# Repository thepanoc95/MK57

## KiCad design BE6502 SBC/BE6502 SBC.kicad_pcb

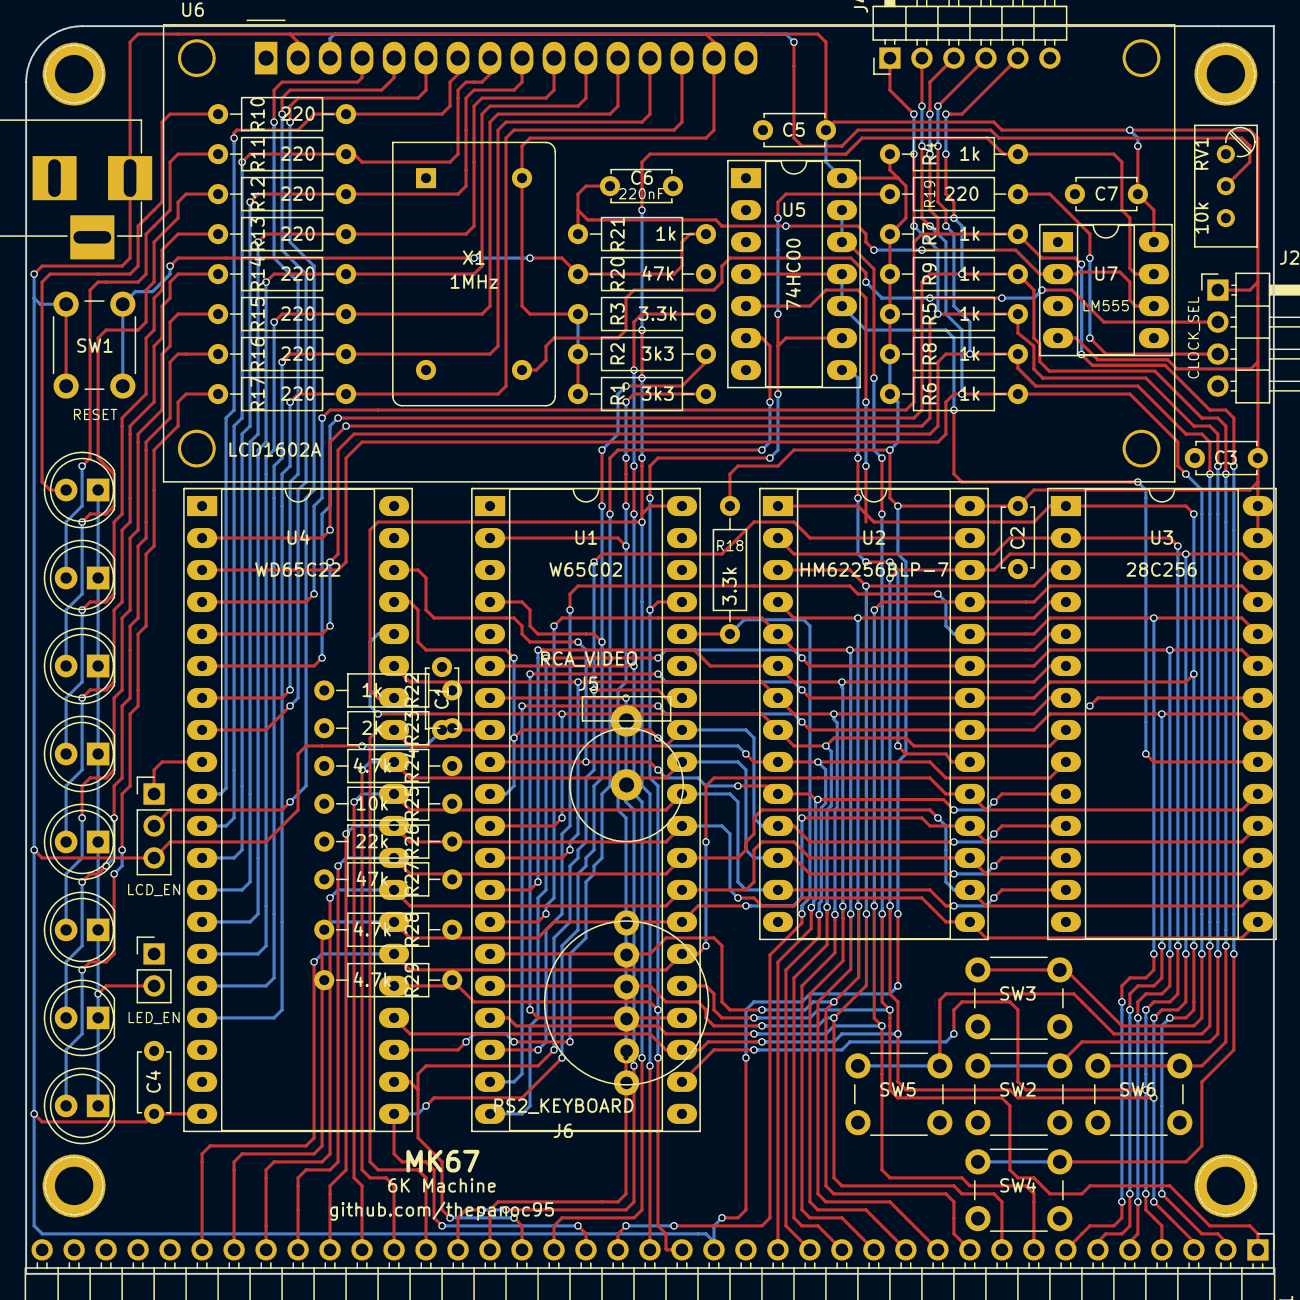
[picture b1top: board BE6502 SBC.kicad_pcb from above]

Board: 2 copper layers, 99.1 x 99.1 mm, 71 parts (0 on the bottom side), 68 nets.

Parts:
C1, C2, C3, C4, C5, C7: 100nF; C_Disc_D4.7mm_W2.5mm_P5.00mm
C6: 220nF; C_Disc_D4.7mm_W2.5mm_P5.00mm
D1, D2, D3, D4, D5, D6, D7, D8: LED; LED_D5.0mm
J1: Expansion; Pin_Header_Angled_1x39_Pitch2.54mm
J2: CLOCK_SEL; Pin_Header_Angled_1x04_Pitch2.54mm
J3: BARREL_JACK
J4: Control; Pin_Header_Angled_1x06_Pitch2.54mm
J5: RCA_VIDEO; RCA_Phono_THT
J6: PS2_KEYBOARD; PS2-6P_MiniDIN_THT
JP1: LED_EN; Pin_Header_Straight_1x02_Pitch2.54mm
JP2: LCD_EN; Pin_Header_Straight_1x03_Pitch2.54mm
M1, M2, M3, M4: Mounting; 1pin
R1, R2: 3k3; R_Axial_DIN0207_L6.3mm_D2.5mm_P10.16mm_Horizontal
R3, R18: 3.3k; R_Axial_DIN0207_L6.3mm_D2.5mm_P10.16mm_Horizontal
R4, R5, R6, R7, R8, R9, R21, R22: 1k; R_Axial_DIN0207_L6.3mm_D2.5mm_P10.16mm_Horizontal
R10, R11, R12, R13, R14, R15, R16, R17, R19: 220; R_Axial_DIN0207_L6.3mm_D2.5mm_P10.16mm_Horizontal
R20, R27: 47k; R_Axial_DIN0207_L6.3mm_D2.5mm_P10.16mm_Horizontal
R23: 2k; R_Axial_DIN0207_L6.3mm_D2.5mm_P10.16mm_Horizontal
R24, R28, R29: 4.7k; R_Axial_DIN0207_L6.3mm_D2.5mm_P10.16mm_Horizontal
R25: 10k; R_Axial_DIN0207_L6.3mm_D2.5mm_P10.16mm_Horizontal
R26: 22k; R_Axial_DIN0207_L6.3mm_D2.5mm_P10.16mm_Horizontal
RV1: 10k; Potentiometer_Trimmer_Bourns_3296W
SW1: RESET; SW_PUSH_6mm
SW2: MIDDLE; SW_PUSH_6mm
SW3: UP; SW_PUSH_6mm
SW4: DOWN; SW_PUSH_6mm
SW5: LEFT; SW_PUSH_6mm
SW6: RIGHT; SW_PUSH_6mm
U1: W65C02; DIP-40_W15.24mm_Socket_LongPads
U2: HM62256BLP-7; DIP-28_W15.24mm_Socket_LongPads
U3: 28C256; DIP-28_W15.24mm_Socket_LongPads
U4: WD65C22; DIP-40_W15.24mm_Socket_LongPads
U5: 74HC00; DIP-14_W7.62mm_Socket_LongPads
U6: RC1602A; WC1602A
U7: LM555; DIP-8_W7.62mm_Socket_LongPads
X1: 1MHz; Oscillator_DIP-14

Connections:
/A0: J1.16, U1.9, U2.10, U3.10, U4.38
/A1: J1.15, U1.10, U2.9, U3.9, U4.37
/A2: J1.14, U1.11, U2.8, U3.8, U4.36
/A3: J1.13, U1.12, U2.7, U3.7, U4.35
/A4: J1.12, U1.13, U2.6, U3.6
/A5: J1.11, U1.14, U2.5, U3.5
/A6: J1.10, U1.15, U2.4, U3.4
/A7: J1.9, U1.16, U2.3, U3.3
/A8: J1.8, U1.17, U2.25, U3.25
/A9: J1.7, U1.18, U2.24, U3.24
/A10: J1.6, U1.19, U2.21, U3.21
/A11: J1.5, U1.20, U2.23, U3.23
/A12: J1.4, U1.22, U2.2, U3.2
/A13: J1.3, U1.23, U2.26, U3.26, U4.24
/A14: J1.2, U1.24, U2.1, U2.22, U3.1, U5.5
/A15: J1.1, U1.25, U5.12, U5.13
/BE: J1.21, R18.1, U1.36
/D0: J1.27, U1.33, U2.11, U3.11, U4.33
/D1: J1.28, U1.32, U2.12, U3.12, U4.32
/D2: J1.29, U1.31, U2.13, U3.13, U4.31
/D3: J1.30, U1.30, U2.15, U3.15, U4.30
/D4: J1.31, U1.29, U2.16, U3.16, U4.29
/D5: J1.32, U1.28, U2.17, U3.17, U4.28
/D6: J1.33, U1.27, U2.18, U3.18, U4.27
/D7: J1.34, U1.26, U2.19, U3.19, U4.26
/PA0: J4.1, R5.2, R22.1, SW2.1, U4.2
/PA1: J4.2, R6.2, R23.1, SW3.1, U4.3
/PA2: J4.3, R7.2, R24.1, SW4.1, U4.4
/PA3: J4.4, R8.2, R25.1, SW5.1, U4.5
/PA4: J4.5, R9.2, R26.1, SW6.1, U4.6
/PA5: R27.1, U4.7, U6.4
/PA6: J6.1, R28.1, U4.8, U6.5
/PA7: J6.5, JP2.1, R29.1, U4.9
/PB0: R10.2, U4.10, U6.7
/PB1: R11.2, U4.11, U6.8
/PB2: R12.2, U4.12, U6.9
/PB3: R13.2, U4.13, U6.10
/PB4: R14.2, U4.14, U6.11
/PB5: R15.2, U4.15, U6.12
/PB6: R16.2, U4.16, U6.13
/PB7: R17.2, U4.17, U6.14
/R/~W: J1.24, U1.34, U2.27, U4.22
/SYNC: J1.26, U1.7
/~IRQ: J1.22, R2.1, U1.4, U4.21
/~NMI: J1.23, R3.1, U1.6
/~RDY: J1.25, R1.1, U1.2
CLOCK: J1.19, R19.1, U1.37, U4.25, U5.9
GND: C1.2, C2.2, C3.2, C4.2, C5.2, C6.2, C7.2, J1.17, J2.4, J3.2, J3.3, J4.6, J5.2, J6.3, JP1.1, R20.2, RV1.1, SW2.2, SW3.2, SW4.2, SW5.2, SW6.2, U1.21, U2.14, U3.14, U3.22, U4.1, U5.1, U5.2, U5.7, U6.1, U6.16, U7.1, X1.7
unnamed: C6.1, R21.1, U7.2, U7.6
unnamed: D1.1, D2.1, D3.1, D4.1, D5.1, D6.1, D7.1, D8.1, JP1.2
unnamed: D1.2, R10.1
unnamed: D2.2, R11.1
unnamed: D3.2, R12.1
unnamed: D4.2, R13.1
unnamed: D5.2, R14.1
unnamed: D6.2, R15.1
unnamed: D7.2, R16.1
unnamed: D8.2, R17.1
unnamed: J2.2, X1.8
unnamed: J2.3, R19.2
unnamed: JP2.2, U6.6
unnamed: R20.1, R21.2, SW1.2
unnamed: RV1.2, U6.3
VCC: C1.1, C2.1, C3.1, C4.1, C5.1, C7.1, J1.18, J2.1, J3.1, J6.4, JP2.3, R1.2, R2.2, R3.2, R4.1, R5.1, R6.1, R7.1, R8.1, R9.1, R18.2, SW1.1, U1.8, U2.28, U3.27, U3.28, U4.20, U5.14, U6.2, U6.15, U7.4, U7.8, X1.14
~RAM: U2.20, U5.8
~RESET: J1.20, R4.2, U1.40, U4.34, U7.7
~ROM: U3.20, U5.4, U5.10, U5.11
~VIA: U4.23, U5.6

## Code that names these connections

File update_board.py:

"""
BE6502 SBC - Add RCA composite video output and PS/2 keyboard port.

Modifies KiCad schematic and cache library to add composite video 
output (VIA PA0-PA5 -> resistor DAC -> RCA) and PS/2 keyboard 
connector (VIA PA6=DATA, PA7=CLOCK -> mini-DIN).

Usage: python3 update_board.py
"""

import os, re, hashlib

SBC_DIR = "/workspaces/MK57/BE6502 SBC"
SCH_FILE = os.path.join(SBC_DIR, "BE6502 SBC.sch")
CACHE_LIB = os.path.join(SBC_DIR, "BE6502 SBC-cache.lib")

CACHE_ADDITIONS = """#
# conn_Conn_01x02
#
DEF conn_Conn_01x02 J 0 40 Y N 1 F N
F0 "J" 0 150 50 H V C CNN
F1 "conn_Conn_01x02" 0 -200 50 H V C CNN
F2 "" 0 0 50 H I C CNN
F3 "" 0 0 50 H I C CNN
$FPLIST
 Connector*:*_??x??_*
 Connector*:*_1x02*
$ENDFPLIST
DRAW
S -50 150 50 -150 1 1 10 f
X Pin_1 1 -200 50 150 R 50 50 1 1 P
X Pin_2 2 -200 -50 150 R 50 50 1 1 P
ENDDRAW
ENDDEF
#
# conn_Conn_01x06
#
DEF conn_Conn_01x06 J 0 40 Y N 1 F N
F0 "J" 0 300 50 H V C CNN
F1 "conn_Conn_01x06" 0 -350 50 H V C CNN
F2 "" 0 0 50 H I C CNN
F3 "" 0 0 50 H I C CNN
$FPLIST
 Connector*:*_??x??_*
 Connector*:*_1x06*
$ENDFPLIST
DRAW
S -50 250 50 -250 1 1 10 f
X Pin_1 1 -200 200 150 R 50 50 1 1 P
X Pin_2 2 -200 100 150 R 50 50 1 1 P
X Pin_3 3 -200 0 150 R 50 50 1 1 P
X Pin_4 4 -200 -100 150 R 50 50 1 1 P
X Pin_5 5 -200 -200 150 R 50 50 1 1 P
X Pin_6 6 -200 -300 150 R 50 50 1 1 P
ENDDRAW
ENDDEF
#
"""

SCH_ADDITIONS = r"""# --- Composite Video RCA Output (VIA PA0-PA5 -> Resistor DAC) ---
$Comp
L Device:R R22
U 1 1 00000001
P 5000 9000
F 0 "R22" V 5080 9000 50  0000 C CNN
F 1 "1k" V 5000 9000 50  0000 C CNN
F 2 "Resistors_THT:R_Axial_DIN0207_L6.3mm_D2.5mm_P10.16mm_Horizontal" V 4930 9000 50  0001 C CNN
F 3 "" H 5000 9000 50  0001 C CNN
	1    5000 9000
	0    1    1    0   
$EndComp
$Comp
L Device:R R23
U 1 1 00000002
P 5000 9150
F 0 "R23" V 5080 9150 50  0000 C CNN
F 1 "2k" V 5000 9150 50  0000 C CNN
F 2 "Resistors_THT:R_Axial_DIN0207_L6.3mm_D2.5mm_P10.16mm_Horizontal" V 4930 9150 50  0001 C CNN
F 3 "" H 5000 9150 50  0001 C CNN
	1    5000 9150
	0    1    1    0   
$EndComp
$Comp
L Device:R R24
U 1 1 00000003
P 5000 9300
F 0 "R24" V 5080 9300 50  0000 C CNN
F 1 "4.7k" V 5000 9300 50  0000 C CNN
F 2 "Resistors_THT:R_Axial_DIN0207_L6.3mm_D2.5mm_P10.16mm_Horizontal" V 4930 9300 50  0001 C CNN
F 3 "" H 5000 9300 50  0001 C CNN
	1    5000 9300
	0    1    1    0   
$EndComp
$Comp
L Device:R R25
U 1 1 00000004
P 5000 9450
F 0 "R25" V 5080 9450 50  0000 C CNN
F 1 "10k" V 5000 9450 50  0000 C CNN
F 2 "Resistors_THT:R_Axial_DIN0207_L6.3mm_D2.5mm_P10.16mm_Horizontal" V 4930 9450 50  0001 C CNN
F 3 "" H 5000 9450 50  0001 C CNN
	1    5000 9450
	0    1    1    0   
$EndComp
$Comp
L Device:R R26
U 1 1 00000005
P 5000 9600
F 0 "R26" V 5080 9600 50  0000 C CNN
F 1 "22k" V 5000 9600 50  0000 C CNN
F 2 "Resistors_THT:R_Axial_DIN0207_L6.3mm_D2.5mm_P10.16mm_Horizontal" V 4930 9600 50  0001 C CNN
F 3 "" H 5000 9600 50  0001 C CNN
	1    5000 9600
	0    1    1    0   
$EndComp
$Comp
L Device:R R27
U 1 1 00000006
P 5000 9750
F 0 "R27" V 5080 9750 50  0000 C CNN
F 1 "47k" V 5000 9750 50  0000 C CNN
F 2 "Resistors_THT:R_Axial_DIN0207_L6.3mm_D2.5mm_P10.16mm_Horizontal" V 4930 9750 50  0001 C CNN
F 3 "" H 5000 9750 50  0001 C CNN
	1    5000 9750
	0    1    1    0   
$EndComp
$Comp
L conn:Conn_01x02 J5
U 1 1 00000007
P 6050 9400
F 0 "J5" H 6050 9625 50  0000 C CNN
F 1 "RCA_VIDEO" H 6050 9125 50  0000 C CNN
F 2 "Connector:RCA_PJRA3x2_SMD" H 6050 9400 50  0001 C CNN
F 3 "" H 6050 9400 50  0001 C CNN
	1    6050 9400
	1    0    0    0   
$EndComp
$Comp
L power:GND #PWR032
U 1 1 00000008
P 5850 9350
F 0 "#PWR032" H 5850 9100 50  0001 C CNN
F 1 "GND" H 5850 9200 50  0000 C CNN
F 2 "" H 5850 9350 50  0001 C CNN
F 3 "" H 5850 9350 50  0001 C CNN
	1    5850 9350
	1    0    0    -1  
$EndComp
Text Label 4050 9000 0    60   ~ 0
PA0
Text Label 4050 9150 0    60   ~ 0
PA1
Text Label 4050 9300 0    60   ~ 0
PA2
Text Label 4050 9450 0    60   ~ 0
PA3
Text Label 4050 9600 0    60   ~ 0
PA4
Text Label 4050 9750 0    60   ~ 0
PA5
Wire Wire Line 4050 9000 4850 9000
Wire Wire Line 4050 9150 4850 9150
Wire Wire Line 4050 9300 4850 9300
Wire Wire Line 4050 9450 4850 9450
Wire Wire Line 4050 9600 4850 9600
Wire Wire Line 4050 9750 4850 9750
Wire Wire Line 5150 9000 5800 9000
Wire Wire Line 5150 9150 5800 9150
Wire Wire Line 5150 9300 5800 9300
Wire Wire Line 5150 9450 5800 9450
Wire Wire Line 5150 9600 5800 9600
Wire Wire Line 5150 9750 5800 9750
Wire Wire Line 5800 9000 5800 9750
Connection ~ 5800 9000
Connection ~ 5800 9150
Connection ~ 5800 9300
Connection ~ 5800 9450
Connection ~ 5800 9600
Connection ~ 5800 9750
Wire Wire Line 5800 9450 5850 9450
# --- PS/2 Keyboard Port (VIA PA6=DATA, PA7=CLOCK -> mini-DIN) ---
$Comp
L conn:Conn_01x06 J6
U 1 1 00000009
P 6050 10300
F 0 "J6" H 6050 10600 50  0000 C CNN
F 1 "PS2_KEYBOARD" H 6050 9975 50  0000 C CNN
F 2 "Connector:PS2-6P" H 6050 10300 50  0001 C CNN
F 3 "" H 6050 10300 50  0001 C CNN
	1    6050 10300
	1    0    0    0   
$EndComp
$Comp
L Device:R R28
U 1 1 0000000A
P 5500 10500
F 0 "R28" V 5580 10500 50  0000 C CNN
F 1 "4.7k" V 5500 10500 50  0000 C CNN
F 2 "Resistors_THT:R_Axial_DIN0207_L6.3mm_D2.5mm_P10.16mm_Horizontal" V 5430 10500 50  0001 C CNN
F 3 "" H 5500 10500 50  0001 C CNN
	1    5500 10500
	0    1    1    0   
$EndComp
$Comp
L Device:R R29
U 1 1 0000000B
P 5500 10100
F 0 "R29" V 5580 10100 50  0000 C CNN
F 1 "4.7k" V 5500 10100 50  0000 C CNN
F 2 "Resistors_THT:R_Axial_DIN0207_L6.3mm_D2.5mm_P10.16mm_Horizontal" V 5430 10100 50  0001 C CNN
F 3 "" H 5500 10100 50  0001 C CNN
	1    5500 10100
	0    1    1    0   
$EndComp
$Comp
L power:VCC #PWR033
U 1 1 0000000C
P 5600 10400
F 0 "#PWR033" H 5600 10250 50  0001 C CNN
F 1 "VCC" H 5600 10550 50  0000 C CNN
F 2 "" H 5600 10400 50  0001 C CNN
F 3 "" H 5600 10400 50  0001 C CNN
	1    5600 10400
	1    0    0    -1  
$EndComp
$Comp
L power:GND #PWR034
U 1 1 0000000D
P 5850 10300
F 0 "#PWR034" H 5850 10050 50  0001 C CNN
F 1 "GND" H 5850 10150 50  0000 C CNN
F 2 "" H 5850 10300 50  0001 C CNN
F 3 "" H 5850 10300 50  0001 C CNN
	1    5850 10300
	1    0    0    -1  
$EndComp
Text Label 4050 9900 0    60   ~ 0
PA6
Text Label 4050 10200 0    60   ~ 0
PA7
Wire Wire Line 4050 9900 5000 9900
Wire Wire Line 4050 10200 5050 10200
Wire Wire Line 5000 9900 5000 10500
Wire Wire Line 5050 10200 5050 10100
Wire Wire Line 5000 10500 5850 10500
Wire Wire Line 5050 10100 5850 10100
Wire Wire Line 5600 10400 5650 10400
Wire Wire Line 5650 10400 5650 10500
Wire Wire Line 5650 10400 5650 10100
Wire Wire Line 5600 10400 5600 10200
Wire Wire Line 5600 10200 5850 10200
Connection ~ 5650 10400
Connection ~ 5600 10400
Connection ~ 5850 10500
NoConn ~ 5850 10400
NoConn ~ 5850 10000
"""

def update_cache_lib():
    with open(CACHE_LIB, 'r') as f:
        content = f.read()
    for sym_name in ('conn_Conn_01x02', 'conn_Conn_01x06'):
        if f'DEF {sym_name}' in content:
            print(f"  {sym_name} already in cache.lib")
        else:
            content += '\n' + CACHE_ADDITIONS
            print(f"  Added {sym_name} to cache.lib")
            break
    with open(CACHE_LIB, 'w') as f:
        f.write(content)

def update_schematic():
    with open(SCH_FILE, 'r') as f:
        content = f.read()
    
    marker = "NoConn ~ 1875 1750"
    pos = content.find(marker)
    if pos == -1:
        print("ERROR: insertion point not found!")
        return False
    
    idx = pos + len(marker)
    content = content[:idx] + '\n' + SCH_ADDITIONS + '\n' + content[idx:]
    
    # Fix placeholder timestamps (replace 0000000x with unique values)
    counter = [0]
    def fix_ts(m):
        counter[0] += 1
        prefix = m.group(1) if m.lastindex else m.group(0)[:5]
        return f'{prefix}{hashlib.md5(f"be65{counter[0]:04d}".encode()).hexdigest()[:8].upper()}'
    content = re.sub(r'(U \d \d )0000000[0-9A-F]', fix_ts, content)
    
    with open(SCH_FILE, 'w') as f:
        f.write(content)
    print("  Schematic updated with RCA + PS/2 sections")
    return True

def main():
    print("BE6502 SBC - Adding RCA + PS/2 ports")
    print("=" * 50)
    update_cache_lib()
    update_schematic()
    print("=" * 50)
    print("Done! Schematic changes:")
    print("  RCA: PA0-PA5 -> 6-resistor DAC -> J5 (RCA_VIDEO)")
    print("  PS/2: PA6 -> R28 pull-up -> J6 pin1(DATA)")
    print("        PA7 -> R29 pull-up -> J6 pin5(CLOCK)")
    print("        J6 pin3=GND, pin4=VCC, pins2/6=NC")

if __name__ == "__main__":
    main()

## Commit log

2026-06-03 make some basic changes
2026-06-04 Add a bunch of stuff
